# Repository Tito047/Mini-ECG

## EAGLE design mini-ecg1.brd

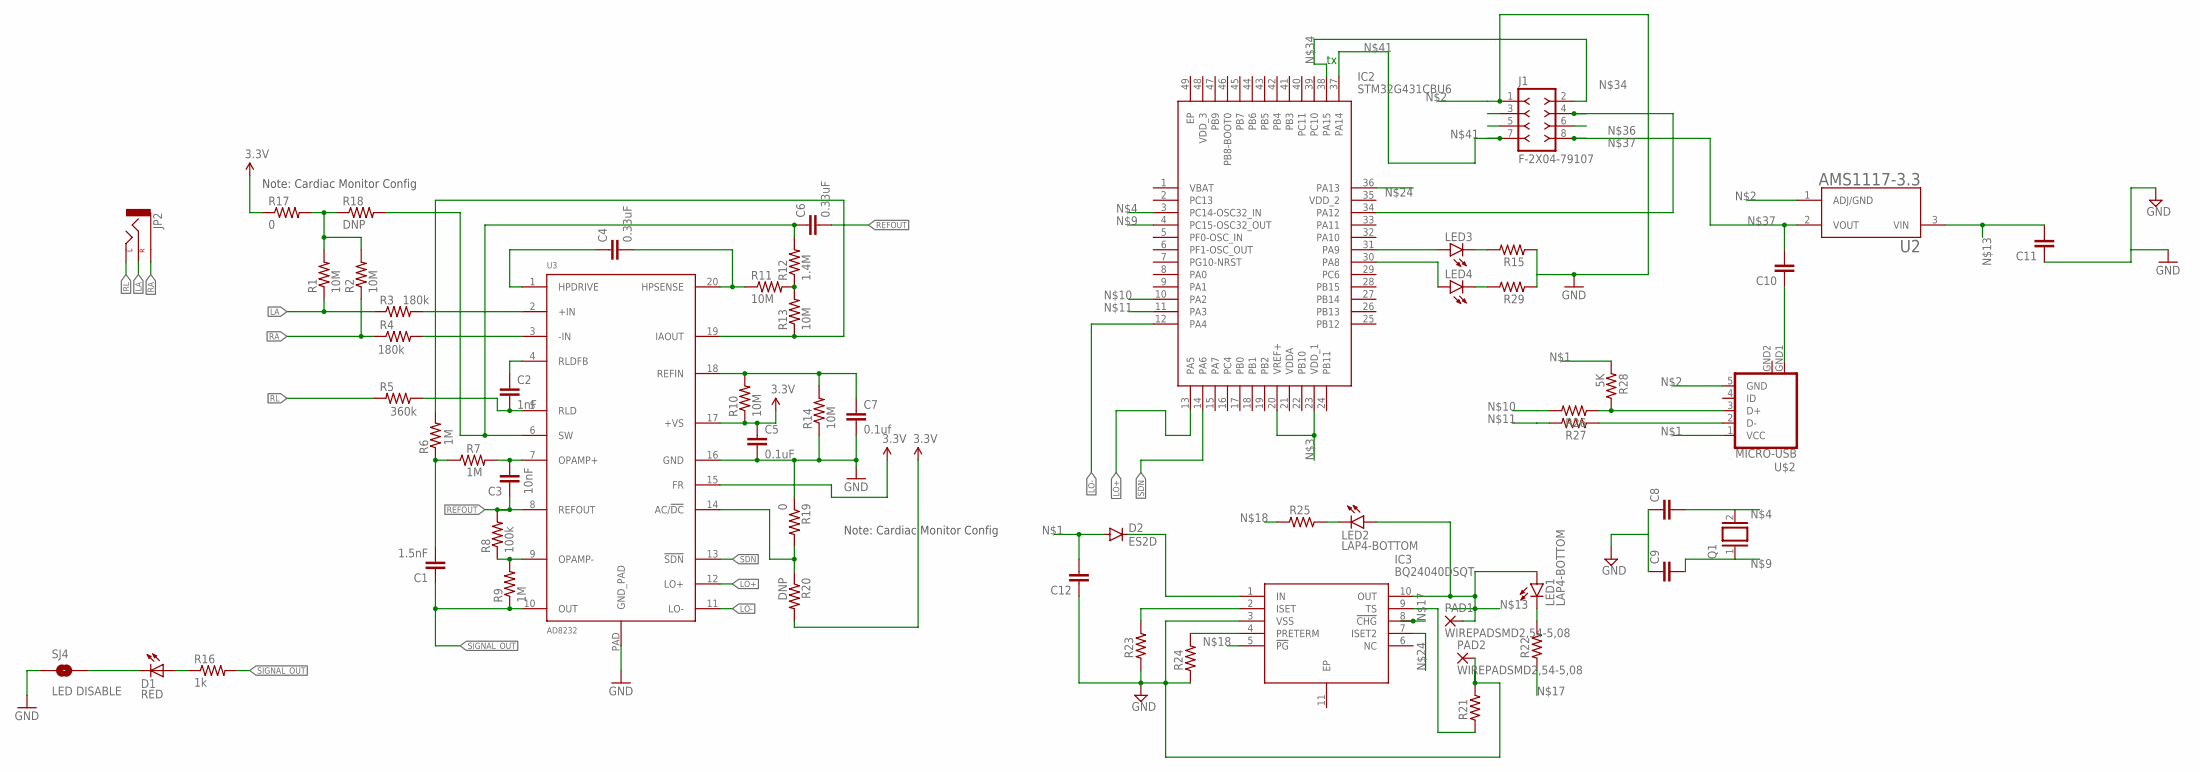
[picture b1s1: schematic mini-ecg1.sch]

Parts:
C1: 1.5nF; 0603-CAP
C2: 1nF; 0603-CAP
C3: 10nF; 0603-CAP
C4, C6: 0.33uF; 0805
C5: 0.1uF; 0603-CAP
C7: 0.1uf; 0603-CAP
C8, C9, C10, C11, C12: C-EUC1206; C1206
D1: RED; LED-0603
D2: ES2D; SMB
IC2: STM32G431CBU6; QFN50P700X700X65-49N
IC3: BQ24040DSQT; SON40P200X200X80-11N
J1: F-2X04-79107; 79107-08
JP2: AUDIO-JACKSMD2; AUDIO-JACK-3.5MM-SMD
LED1, LED2: LAP4-BOTTOM; P47F-BOTTOM
LED3, LED4: LEDCHIPLED_1206; CHIPLED_1206
PAD1, PAD2: WIREPADSMD2,54-5,08; SMD2,54-5,08
Q1: XTAL/S; QS
R1, R2, R10, R11, R13, R14: 10M; 0603-RES
R3, R4: 180k; 0603-RES
R5: 360k; 0603-RES
R6, R7, R9: 1M; 0603-RES
R8: 100k; 0603-RES
R12: 1.4M; 0603-RES
R15, R21, R22, R23, R24, R25, R26, R27, R29: R_1206; R1206
R16: 1k; 0603-RES
R17, R19: 0; 0603
R18, R20: DNP; 0603
R28: 5K; R1206
SJ4: LED DISABLE; SJ_2S-TRACE
U2: AMS1117-3.3; SOT229P700X180-4N
U3: AD8232; LFCSP_20
U$2: MICRO-USB

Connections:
3.3V: C5.1, R10.1, R17.1, R20.2, U3.15 (FR), U3.17 (+VS)
GND: C5.2, C7.2, C11.1, C12.1, IC3.3 (VSS), PAD2.1, R14.1, R19.1, R21.2, R23.1, R24.1, SJ4.1, U3.16 (GND), U3.PAD (GND_PAD), U$2.GND2 (GND)
LA: JP2.RING (RIGHT), R1.1, R3.1
LO+: IC2.13 (PA5), U3.12 (LO+)
LO-: IC2.12 (PA4), U3.11 (LO-)
unnamed: C12.2, D2.A, R28.1, U$2.1 (VCC)
unnamed: J1.1, R15.1, R29.1, U2.1 (ADJ/GND), U$2.5 (GND)
unnamed: IC2.20 (VREF+), IC2.23 (VDD_1), R3.2, U3.2 (+IN)
unnamed: IC2.3 (PC14-OSC32_IN), R4.2, U3.3 (-IN)
unnamed: C3.2, R7.2, U3.7 (OPAMP+)
unnamed: C4.2, R11.1, U3.20 (HPSENSE)
unnamed: C7.1, R10.2, R14.2, U3.18 (REFIN)
unnamed: R8.1, R9.2, U3.9 (OPAMP-)
unnamed: C1.2, IC2.4 (PC15-OSC32_OUT), R6.1, R7.1
unnamed: IC2.10 (PA2), R26.1, R28.2, U$2.3 (D+)
unnamed: C10.1, U$2.GND1 (GND)
unnamed: C4.1, C11.2, IC3.10 (OUT), LED1.A, LED2.A, PAD1.1, U2.3 (VIN), U3.1 (HPDRIVE)
unnamed: R11.2, R12.1, R13.2
unnamed: R6.2, R13.1, U3.19 (IAOUT)
unnamed: C6.1, R12.2, R18.2, U3.6 (SW)
unnamed: C2.1, IC3.8 (!CHG), R22.1, U3.4 (RLDFB)
unnamed: C2.2, IC3.5 (!PG), R5.1, R25.1, U3.5 (RLD)
unnamed: D1.A, R16.1
unnamed: R1.2, R2.2, R17.2, R18.1
unnamed: D1.C, SJ4.2
unnamed: R19.2, R20.1, U3.14 (AC/!DC)
unnamed: C8.2, Q1.2
unnamed: C9.2, IC2.36 (PA13), IC3.7 (ISET2), LED2.C, Q1.1, R25.2
unnamed: C8.1, C9.1
unnamed: IC3.9 (TS), R21.1
unnamed: LED1.C, R22.2
unnamed: IC3.2 (ISET), R23.2
unnamed: IC3.4 (PRETERM), R24.2
unnamed: D2.C, IC3.1 (IN)
unnamed: R27.1, U$2.2 (D-)
unnamed: IC2.38 (PA15), J1.2
unnamed: IC2.34 (PA12), J1.4
unnamed: C10.2, J1.8, U2.2 (VOUT)
unnamed: IC2.37 (PA14), J1.7
unnamed: IC2.31 (PA9), LED3.A
unnamed: LED3.C, R15.2
unnamed: IC2.30 (PA8), LED4.A
unnamed: LED4.C, R29.2
RA: JP2.SLEEVE, R2.1, R4.1
REFOUT: C3.1, C6.2, R8.2, U3.8 (REFOUT)
RL: JP2.TIP (LEFT), R5.2
SDN: IC2.14 (PA6), U3.13 (!SDN)
SIGNAL_OUT: C1.1, R9.1, R16.2, U3.10 (OUT)

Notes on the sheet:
Note: Cardiac Monitor Config

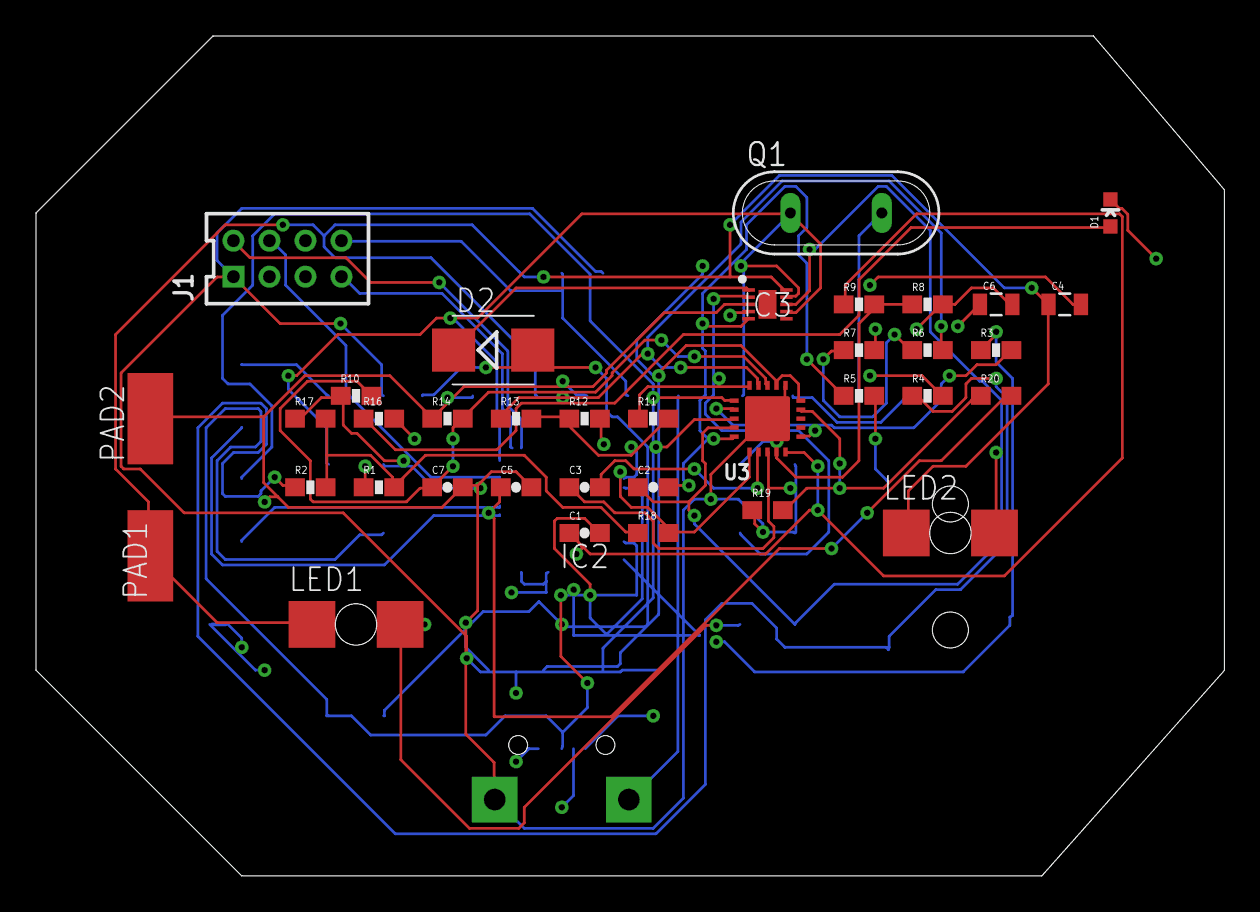
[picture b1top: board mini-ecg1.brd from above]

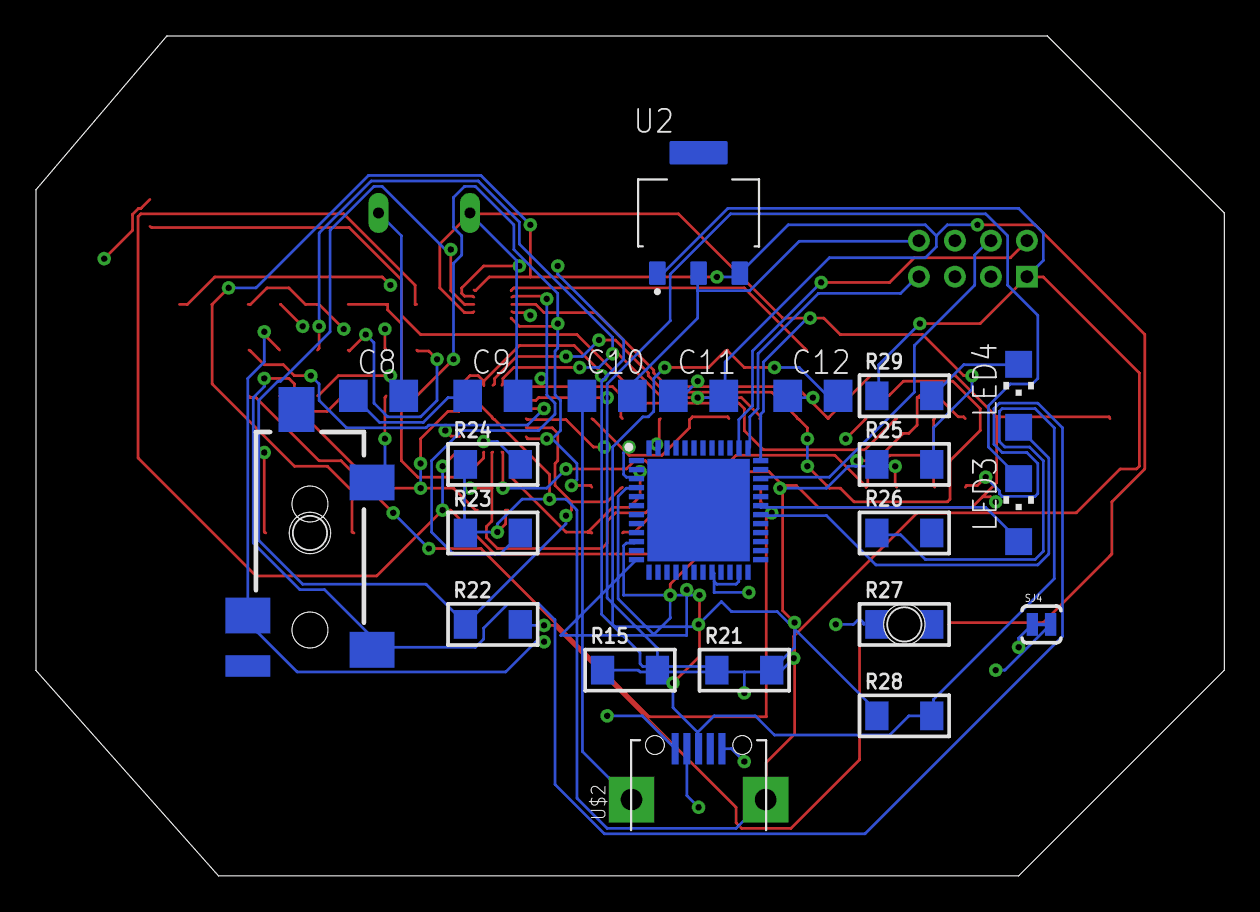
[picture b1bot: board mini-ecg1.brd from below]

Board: 6 copper layers, 66.0 x 46.7 mm, 58 parts (22 on the bottom side), 48 nets.

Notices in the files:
parts and their libraries:
SparkFun-Passives: Licensing: CC v3.0 Share-Alike You are welcome to use this library for commercial purposes.
con-headers-jp: Copyright (C) 2008, Bob Starr
rc-master-smd: Copyright (C) 2007, Bob Starr
